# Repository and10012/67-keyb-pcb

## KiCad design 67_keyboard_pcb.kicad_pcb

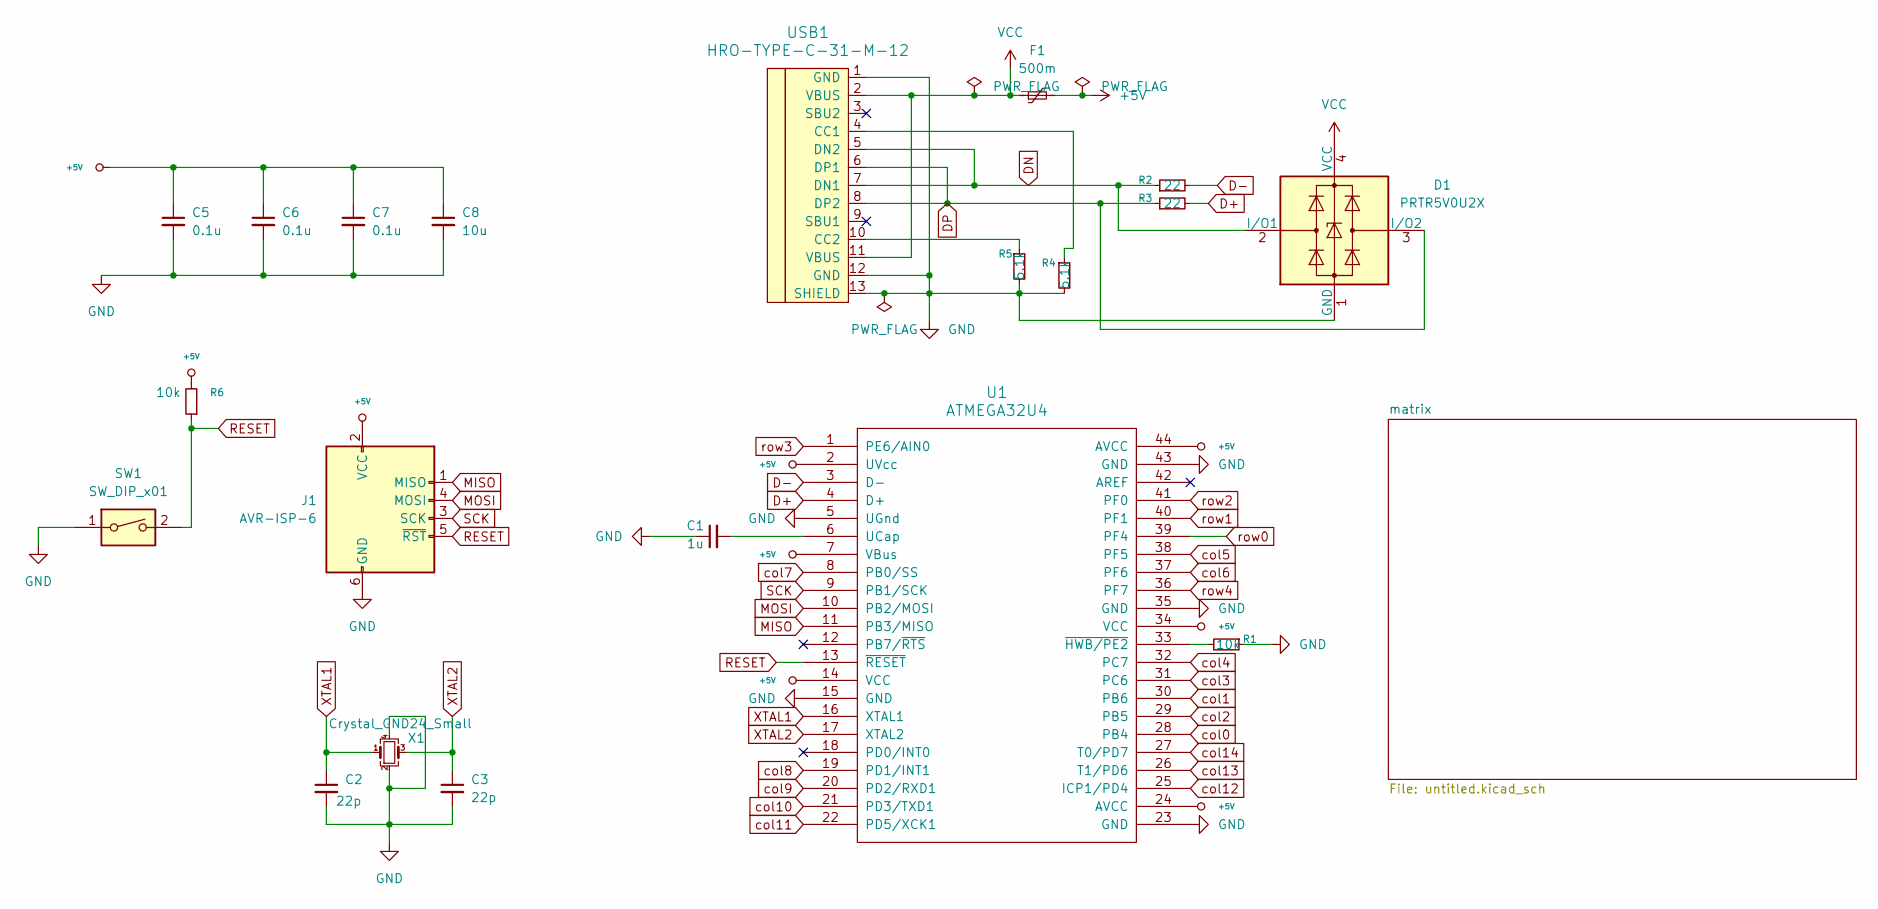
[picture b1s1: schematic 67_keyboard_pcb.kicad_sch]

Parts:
C1: 1u; C_0805_2012Metric_Pad1.18x1.45mm_HandSolder
C2, C3: 22p; C_0805_2012Metric_Pad1.18x1.45mm_HandSolder
C5, C6, C7: 0.1u; C_0805_2012Metric_Pad1.18x1.45mm_HandSolder
C8: 10u; C_0805_2012Metric_Pad1.18x1.45mm_HandSolder
D1: PRTR5V0U2X; SOT143B
F1: 500m; Fuse_1206_3216Metric_Pad1.42x1.75mm_HandSolder
J1: AVR-ISP-6; Reset_Pretty-Mask
R1, R6: 10k; R_0805_2012Metric_Pad1.20x1.40mm_HandSolder
R2, R3: 22; R_0805_2012Metric_Pad1.20x1.40mm_HandSolder
R4, R5: 5.1k; R_0805_2012Metric_Pad1.20x1.40mm_HandSolder
SW1: SW_DIP_x01; SW_SPST_SKQG_WithStem
U1: ATMEGA32U4; TQFP-44_10x10mm_P0.8mm
USB1: HRO-TYPE-C-31-M-12; HRO-TYPE-C-31-M-12-HandSoldering
X1: Crystal_GND24_Small; Crystal_SMD_3225-4Pin_3.2x2.5mm_HandSoldering

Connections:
+5V: C5.1, C6.1, C7.1, C8.1, F1.2, J1.2 (VCC), R6.2, U1.2 (UVcc), U1.7 (VBus), U1.14 (VCC), U1.24 (AVCC), U1.34 (VCC), U1.44 (AVCC)
D+: R3.2, U1.4 (D+)
D-: R2.2, U1.3 (D-)
DN: D1.2 (I/O1), R2.1, USB1.5 (DN2), USB1.7 (DN1)
DP: D1.3 (I/O2), R3.1, USB1.6 (DP1), USB1.8 (DP2)
GND: C1.1, C2.2, C3.2, C5.2, C6.2, C7.2, C8.2, D1.1 (GND), J1.6 (GND), R1.1, R4.2, R5.2, SW1.1, U1.5 (UGnd), U1.15 (GND), U1.23 (GND), U1.35 (GND), U1.43 (GND), USB1.1 (GND), USB1.12 (GND), USB1.13 (SHIELD), X1.2, X1.4
MISO: J1.1 (MISO), U1.11 (PB3/MISO)
MOSI: J1.4 (MOSI), U1.10 (PB2/MOSI)
unnamed: C1.2, U1.6 (UCap)
unnamed: R1.2, U1.33 (~HWB/PE2)
unnamed: R4.1, USB1.4 (CC1)
unnamed: R5.1, USB1.10 (CC2)
RESET: J1.5 (~RST), R6.1, SW1.2, U1.13 (~RESET)
SCK: J1.3 (SCK), U1.9 (PB1/SCK)
VCC: D1.4 (VCC), F1.1, USB1.2 (VBUS), USB1.11 (VBUS)
XTAL1: C2.1, U1.16 (XTAL1), X1.1
XTAL2: C3.1, U1.17 (XTAL2), X1.3
col0: U1.28 (PB4); also elsewhere on the board
col1: U1.30 (PB6); also elsewhere on the board
col2: U1.29 (PB5); also elsewhere on the board
col3: U1.31 (PC6); also elsewhere on the board
col4: U1.32 (PC7); also elsewhere on the board
col5: U1.38 (PF5); also elsewhere on the board
col6: U1.37 (PF6); also elsewhere on the board
col7: U1.8 (PB0/SS); also elsewhere on the board
col8: U1.19 (PD1/INT1); also elsewhere on the board
col9: U1.20 (PD2/RXD1); also elsewhere on the board
col10: U1.21 (PD3/TXD1); also elsewhere on the board
col11: U1.22 (PD5/XCK1); also elsewhere on the board
col12: U1.25 (ICP1/PD4); also elsewhere on the board
col13: U1.26 (T1/PD6); also elsewhere on the board
col14: U1.27 (T0/PD7); also elsewhere on the board
row0: U1.39 (PF4); also elsewhere on the board
row1: U1.40 (PF1); also elsewhere on the board
row2: U1.41 (PF0); also elsewhere on the board
row3: U1.1 (PE6/AIN0); also elsewhere on the board
row4: U1.36 (PF7); also elsewhere on the board

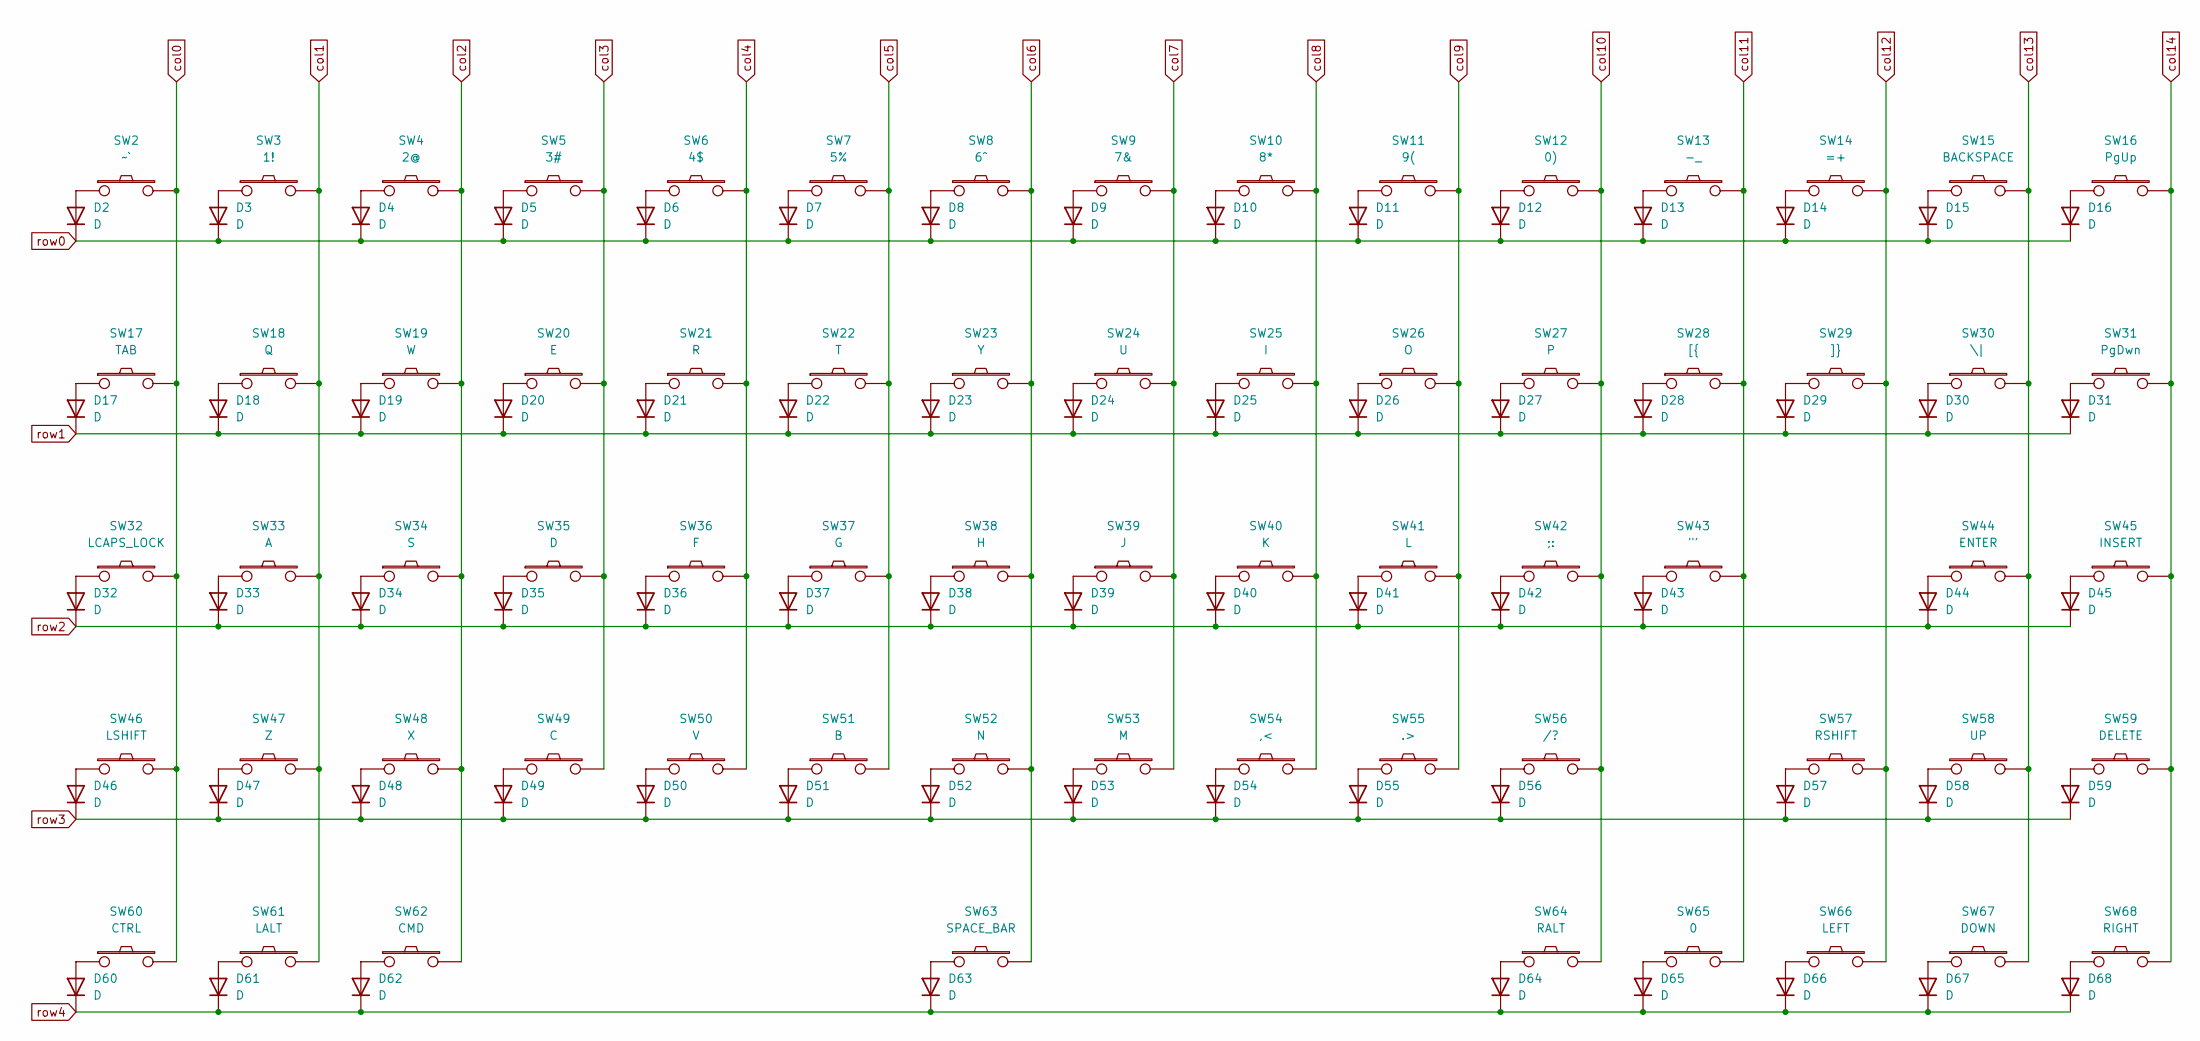
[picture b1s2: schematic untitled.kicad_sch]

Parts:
D2, D3, D4, D5, D6, D7, D8, D9, D10, D11, D12, D13, D14, D15, D16, D17, D18, D19, D20, D21, D22, D23, D24, D25, D26, D27, D28, D29, D30, D31, D32, D33, D34, D35, D36, D37, D38, D39, D40, D41, D42, D43, D44, D45, D46, D47, D48, D49, D50, D51, D52, D53, D54, D55, D56, D57, D58, D59, D60, D61, D62, D63, D64, D65, D66, D67, D68: D; D_SOD-123
SW2: ~`; MX-Hotswap-1U
SW3: 1!; MX-Hotswap-1U
SW4: 2@; MX-Hotswap-1U
SW5: 3#; MX-Hotswap-1U
SW6: 4$; MX-Hotswap-1U
SW7: 5%; MX-Hotswap-1U
SW8: 6^; MX-Hotswap-1U
SW9: 7&; MX-Hotswap-1U
SW10: 8*; MX-Hotswap-1U
SW11: 9(; MX-Hotswap-1U
SW12: 0); MX-Hotswap-1U
SW13: -_; MX-Hotswap-1U
SW14: =+; MX-Hotswap-1U
SW15: BACKSPACE; MX-Hotswap-2U
SW16: PgUp; MX-Hotswap-1U
SW17: TAB; MX-Hotswap-1.5U
SW18: Q; MX-Hotswap-1U
SW19: W; MX-Hotswap-1U
SW20: E; MX-Hotswap-1U
SW21: R; MX-Hotswap-1U
SW22: T; MX-Hotswap-1U
SW23: Y; MX-Hotswap-1U
SW24: U; MX-Hotswap-1U
SW25: I; MX-Hotswap-1U
SW26: O; MX-Hotswap-1U
SW27: P; MX-Hotswap-1U
SW28: [{; MX-Hotswap-1U
SW29: ]}; MX-Hotswap-1U
SW30: \|; MX-Hotswap-1.5U
SW31: PgDwn; MX-Hotswap-1U
SW32: LCAPS_LOCK; MX-Hotswap-1.75U
SW33: A; MX-Hotswap-1U
SW34: S; MX-Hotswap-1U
SW35: D; MX-Hotswap-1U
SW36: F; MX-Hotswap-1U
SW37: G; MX-Hotswap-1U
SW38: H; MX-Hotswap-1U
SW39: J; MX-Hotswap-1U
SW40: K; MX-Hotswap-1U
SW41: L; MX-Hotswap-1U
SW42: ;:; MX-Hotswap-1U
SW43: "'; MX-Hotswap-1U
SW44: ENTER; MX-Hotswap-2.25U
SW45: INSERT; MX-Hotswap-1U
SW46: LSHIFT; MX-Hotswap-2.25U
SW47: Z; MX-Hotswap-1U
SW48: X; MX-Hotswap-1U
SW49: C; MX-Hotswap-1U
SW50: V; MX-Hotswap-1U
SW51: B; MX-Hotswap-1U
SW52: N; MX-Hotswap-1U
SW53: M; MX-Hotswap-1U
SW54: ,<; MX-Hotswap-1U
SW55: .>; MX-Hotswap-1U
SW56: /?; MX-Hotswap-1U
SW57: RSHIFT; MX-Hotswap-1.75U
SW58: UP; MX-Hotswap-1U
SW59: DELETE; MX-Hotswap-1U
SW60: CTRL; MX-Hotswap-1.5U
SW61: LALT; MX-Hotswap-1.25U
SW62: CMD; MX-Hotswap-1.5U
SW63: SPACE_BAR; MX-Hotswap-6.25U
SW64: RALT; MX-Hotswap-1.25U
SW65: 0; MX-Hotswap-1.25U
SW66: LEFT; MX-Hotswap-1U
SW67: DOWN; MX-Hotswap-1U
SW68: RIGHT; MX-Hotswap-1U

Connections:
unnamed: D2.2 (A), SW2.1
unnamed: D3.2 (A), SW3.1
unnamed: D4.2 (A), SW4.1
unnamed: D5.2 (A), SW5.1
unnamed: D6.2 (A), SW6.1
unnamed: D7.2 (A), SW7.1
unnamed: D8.2 (A), SW8.1
unnamed: D9.2 (A), SW9.1
unnamed: D10.2 (A), SW10.1
unnamed: D11.2 (A), SW11.1
unnamed: D12.2 (A), SW12.1
unnamed: D13.2 (A), SW13.1
unnamed: D14.2 (A), SW14.1
unnamed: D15.2 (A), SW15.1
unnamed: D16.2 (A), SW16.1
unnamed: D17.2 (A), SW17.1
unnamed: D18.2 (A), SW18.1
unnamed: D19.2 (A), SW19.1
unnamed: D20.2 (A), SW20.1
unnamed: D21.2 (A), SW21.1
unnamed: D22.2 (A), SW22.1
unnamed: D23.2 (A), SW23.1
unnamed: D24.2 (A), SW24.1
unnamed: D25.2 (A), SW25.1
unnamed: D26.2 (A), SW26.1
unnamed: D27.2 (A), SW27.1
unnamed: D28.2 (A), SW28.1
unnamed: D29.2 (A), SW29.1
unnamed: D30.2 (A), SW30.1
unnamed: D31.2 (A), SW31.1
unnamed: D32.2 (A), SW32.1
unnamed: D33.2 (A), SW33.1
unnamed: D34.2 (A), SW34.1
unnamed: D35.2 (A), SW35.1
unnamed: D36.2 (A), SW36.1
unnamed: D37.2 (A), SW37.1
unnamed: D38.2 (A), SW38.1
unnamed: D39.2 (A), SW39.1
unnamed: D40.2 (A), SW40.1
unnamed: D41.2 (A), SW41.1
unnamed: D42.2 (A), SW42.1
unnamed: D43.2 (A), SW43.1
unnamed: D44.2 (A), SW44.1
unnamed: D45.2 (A), SW45.1
unnamed: D46.2 (A), SW46.1
unnamed: D47.2 (A), SW47.1
unnamed: D48.2 (A), SW48.1
unnamed: D49.2 (A), SW49.1
unnamed: D50.2 (A), SW50.1
unnamed: D51.2 (A), SW51.1
unnamed: D52.2 (A), SW52.1
unnamed: D53.2 (A), SW53.1
unnamed: D54.2 (A), SW54.1
unnamed: D55.2 (A), SW55.1
unnamed: D56.2 (A), SW56.1
unnamed: D57.2 (A), SW57.1
unnamed: D58.2 (A), SW58.1
unnamed: D59.2 (A), SW59.1
unnamed: D60.2 (A), SW60.1
unnamed: D61.2 (A), SW61.1
unnamed: D62.2 (A), SW62.1
unnamed: D63.2 (A), SW63.1
unnamed: D64.2 (A), SW64.1
unnamed: D65.2 (A), SW65.1
unnamed: D66.2 (A), SW66.1
unnamed: D67.2 (A), SW67.1
unnamed: D68.2 (A), SW68.1
col0: SW2.2, SW17.2, SW32.2, SW46.2, SW60.2; also elsewhere on the board
col1: SW3.2, SW18.2, SW33.2, SW47.2, SW61.2; also elsewhere on the board
col2: SW4.2, SW19.2, SW34.2, SW48.2, SW62.2; also elsewhere on the board
col3: SW5.2, SW20.2, SW35.2, SW49.2; also elsewhere on the board
col4: SW6.2, SW21.2, SW36.2, SW50.2; also elsewhere on the board
col5: SW7.2, SW22.2, SW37.2, SW51.2; also elsewhere on the board
col6: SW8.2, SW23.2, SW38.2, SW52.2, SW63.2; also elsewhere on the board
col7: SW9.2, SW24.2, SW39.2, SW53.2; also elsewhere on the board
col8: SW10.2, SW25.2, SW40.2, SW54.2; also elsewhere on the board
col9: SW11.2, SW26.2, SW41.2, SW55.2; also elsewhere on the board
col10: SW12.2, SW27.2, SW42.2, SW56.2, SW64.2; also elsewhere on the board
col11: SW13.2, SW28.2, SW43.2, SW65.2; also elsewhere on the board
col12: SW14.2, SW29.2, SW57.2, SW66.2; also elsewhere on the board
col13: SW15.2, SW30.2, SW44.2, SW58.2, SW67.2; also elsewhere on the board
col14: SW16.2, SW31.2, SW45.2, SW59.2, SW68.2; also elsewhere on the board
row0: D2.1 (K), D3.1 (K), D4.1 (K), D5.1 (K), D6.1 (K), D7.1 (K), D8.1 (K), D9.1 (K), D10.1 (K), D11.1 (K), D12.1 (K), D13.1 (K), D14.1 (K), D15.1 (K), D16.1 (K); also elsewhere on the board
row1: D17.1 (K), D18.1 (K), D19.1 (K), D20.1 (K), D21.1 (K), D22.1 (K), D23.1 (K), D24.1 (K), D25.1 (K), D26.1 (K), D27.1 (K), D28.1 (K), D29.1 (K), D30.1 (K), D31.1 (K); also elsewhere on the board
row2: D32.1 (K), D33.1 (K), D34.1 (K), D35.1 (K), D36.1 (K), D37.1 (K), D38.1 (K), D39.1 (K), D40.1 (K), D41.1 (K), D42.1 (K), D43.1 (K), D44.1 (K), D45.1 (K); also elsewhere on the board
row3: D46.1 (K), D47.1 (K), D48.1 (K), D49.1 (K), D50.1 (K), D51.1 (K), D52.1 (K), D53.1 (K), D54.1 (K), D55.1 (K), D56.1 (K), D57.1 (K), D58.1 (K), D59.1 (K); also elsewhere on the board
row4: D60.1 (K), D61.1 (K), D62.1 (K), D63.1 (K), D64.1 (K), D65.1 (K), D66.1 (K), D67.1 (K), D68.1 (K); also elsewhere on the board

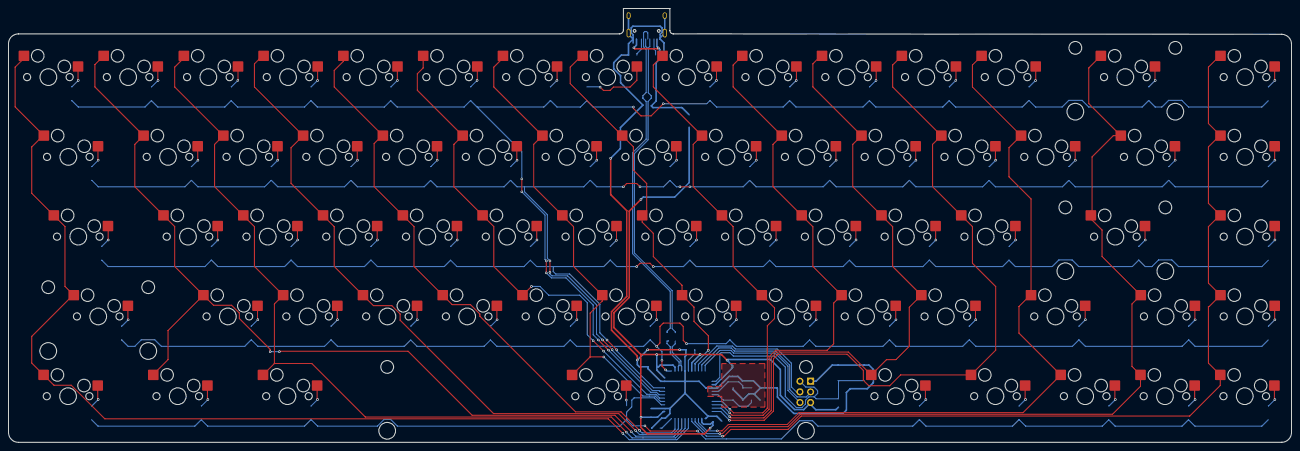
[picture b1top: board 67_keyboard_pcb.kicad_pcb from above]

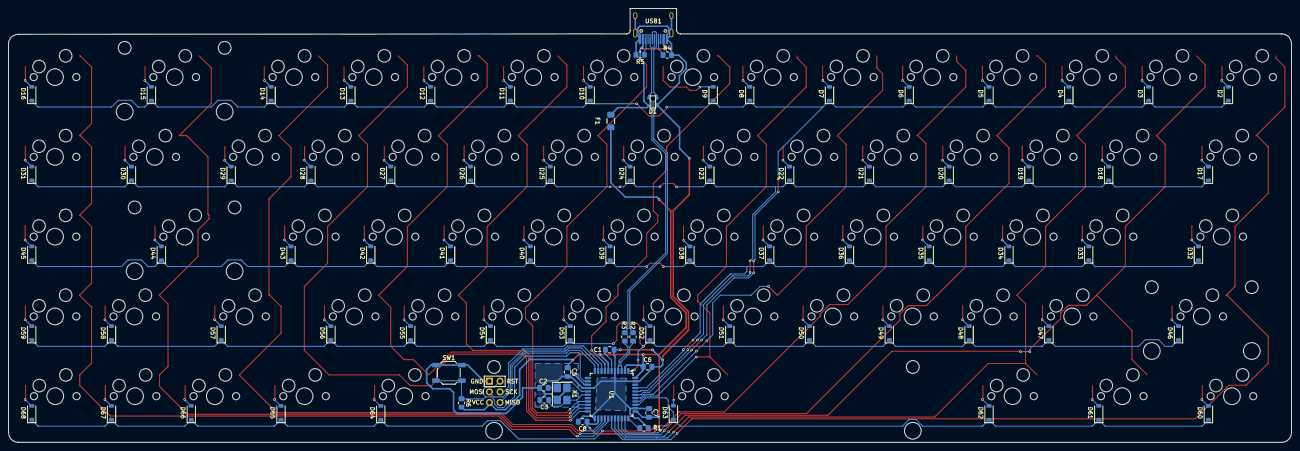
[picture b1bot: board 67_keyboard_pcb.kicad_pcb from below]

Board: 2 copper layers, 306.4 x 103.6 mm, 154 parts (87 on the bottom side), 104 nets.
